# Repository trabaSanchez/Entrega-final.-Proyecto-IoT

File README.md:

# Entrega-final.-Proyecto-IoT
Este repositorio contiene el compendio final, desarrollado por los estudiantes de ingenieria, Cristian Montaño, Jhonatan Rodríguez e Iván Sánchez. Para la materia de diseño de dispositivos IoT.

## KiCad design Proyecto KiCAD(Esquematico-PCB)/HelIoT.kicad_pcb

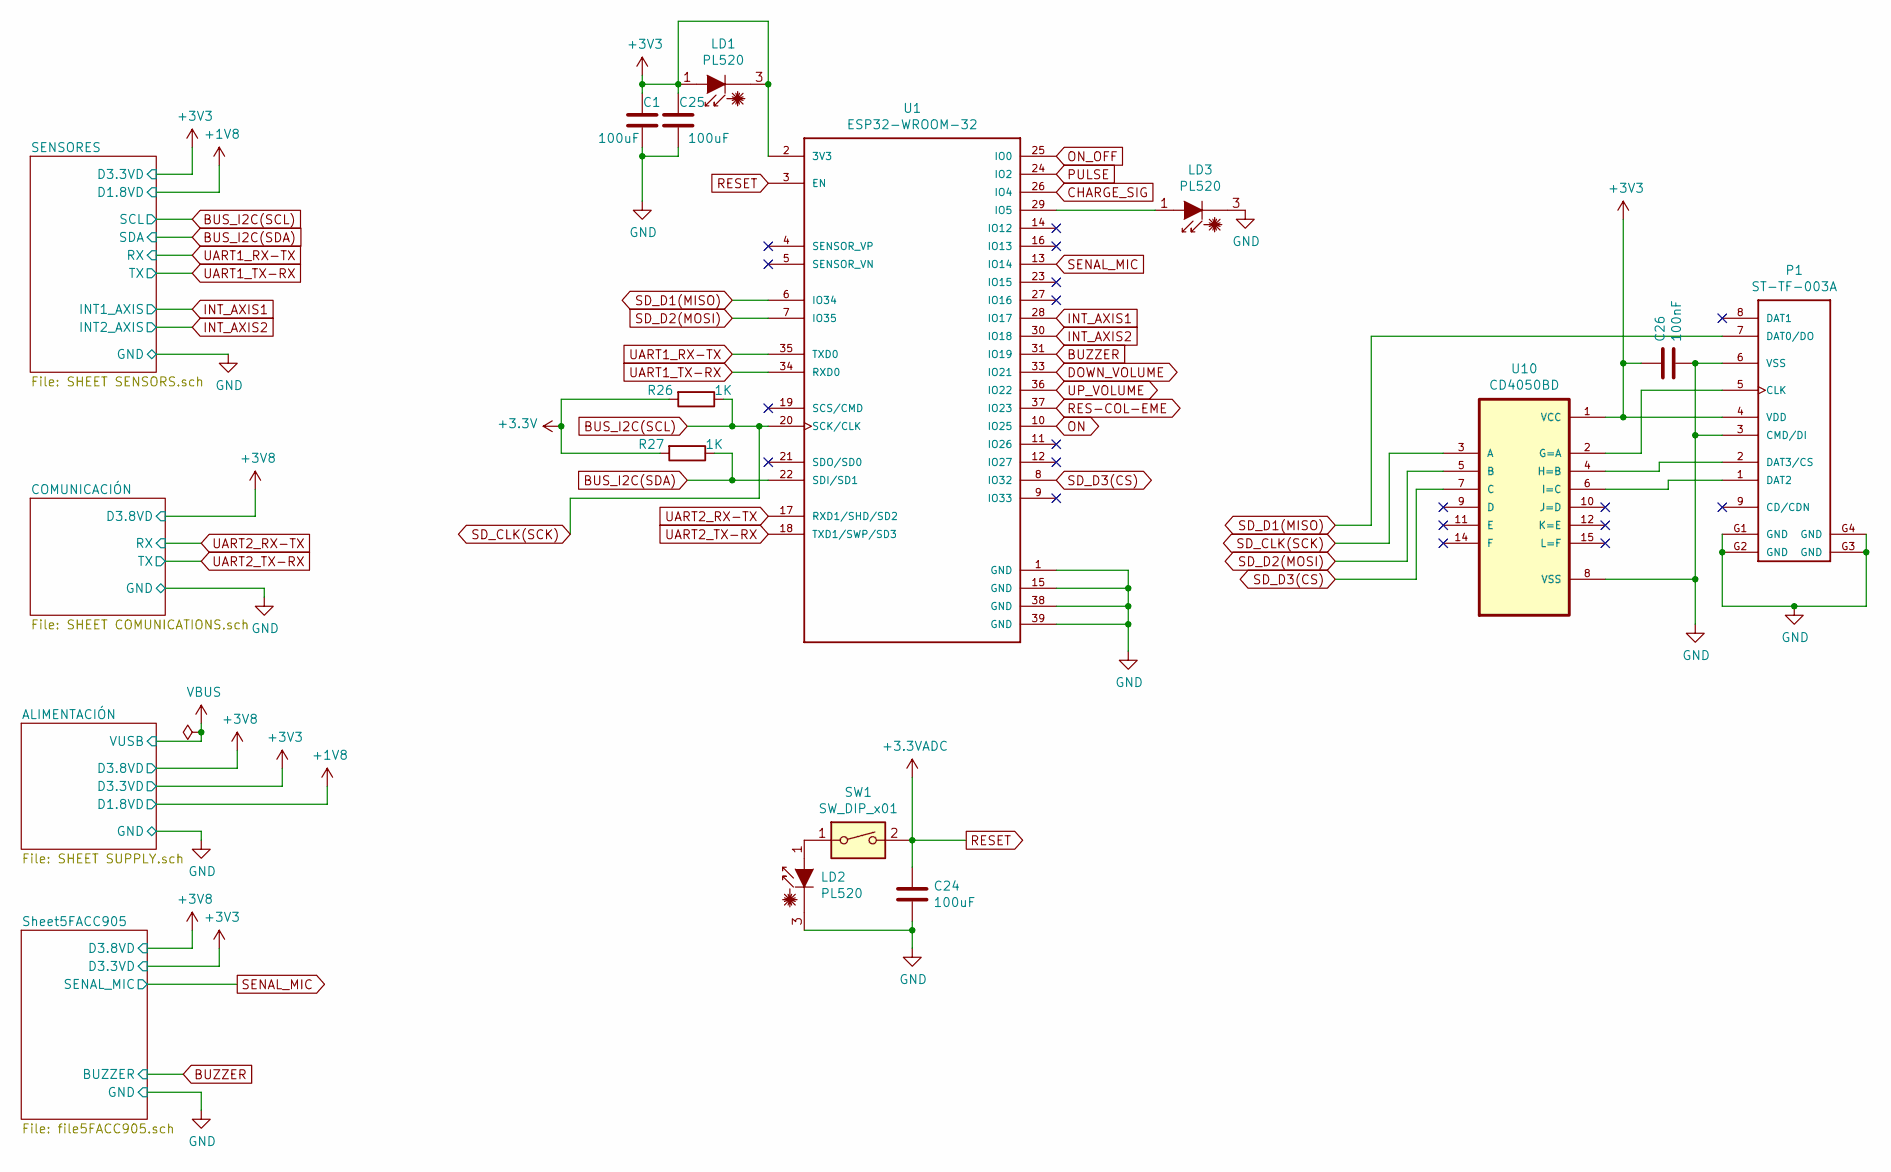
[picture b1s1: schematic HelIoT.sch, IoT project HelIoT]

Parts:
C1, C24, C25: 100uF; C_0603_1608Metric_Pad1.08x0.95mm_HandSolder
C26: 100nF; C_0603_1608Metric_Pad1.08x0.95mm_HandSolder
LD1, LD2, LD3: PL520; LaserDiode_TO38ICut-3
P1: ST-TF-003A; SUNTECH_ST-TF-003A
R26, R27: 1K; R_0402_1005Metric_Pad0.72x0.64mm_HandSolder
SW1: SW_DIP_x01; SW_SPST_REED_CT05-XXXX-G1
U1: ESP32-WROOM-32; MODULE_ESP32-WROOM-32
U10: CD4050BD; SOIC127P600X175-16N

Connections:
BUS_I2C(SCL): R26.1, U1.20 (SCK/CLK), U10.3 (A); also elsewhere on the board
BUS_I2C(SDA): R27.1, U1.22 (SDI/SD1); also elsewhere on the board
BUZZER: U1.31 (IO19); also elsewhere on the board
CHARGE_SIG: U1.26 (IO4); also elsewhere on the board
GND: C1.2, C24.2, C25.2, C26.2, LD2.3 (C), LD3.3 (C), P1.3 (CMD/DI), P1.6 (VSS), P1.G1 (GND), P1.G2 (GND), P1.G3 (GND), P1.G4 (GND), U1.1 (GND), U1.15 (GND), U1.38 (GND), U1.39 (GND), U10.8 (VSS); also elsewhere on the board
INT_AXIS1: U1.28 (IO17); also elsewhere on the board
INT_AXIS2: U1.30 (IO18); also elsewhere on the board
unnamed: LD2.1 (A), SW1.1
unnamed: LD3.1 (A), U1.29 (IO5)
unnamed: P1.1 (DAT2), U10.6 (I=C)
unnamed: P1.2 (DAT3/CS), U10.4 (H=B)
unnamed: P1.5 (CLK), U10.2 (G=A)
ON_OFF: U1.25 (IO0); also elsewhere on the board
PULSE: U1.24 (IO2); also elsewhere on the board
RESET: C24.1, SW1.2, U1.3 (EN); also elsewhere on the board
RXSIM: U1.18 (TXD1/SWP/SD3); also elsewhere on the board
SD_D1(MISO): P1.7 (DAT0/DO), U1.6 (IO34)
SD_D2(MOSI): U1.7 (IO35), U10.5 (B)
SD_D3(CS): U1.8 (IO32), U10.7 (C)
SENAL_MIC: U1.13 (IO14); also elsewhere on the board
TXSIM: U1.17 (RXD1/SHD/SD2); also elsewhere on the board
UART1_RX-TX: U1.35 (TXD0); also elsewhere on the board
UART1_TX-RX: U1.34 (RXD0); also elsewhere on the board
V2: C1.1, C25.1, C26.1, LD1.1 (A), LD1.3 (C), P1.4 (VDD), R26.2, R27.2, U1.2 (3V3), U10.1 (VCC); also elsewhere on the board

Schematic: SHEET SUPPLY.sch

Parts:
C2: 22uF; C_0504_1310Metric_Pad0.83x1.28mm_HandSolder
C3, C11: 1uF; C_0402_1005Metric_Pad0.74x0.62mm_HandSolder
C4: 10uF; C_0402_1005Metric_Pad0.74x0.62mm_HandSolder
C5: 22uF; C_0402_1005Metric_Pad0.74x0.62mm_HandSolder
C8, C9: 0.47uF; C_0402_1005Metric_Pad0.74x0.62mm_HandSolder
C10: 100uF; C_0603_1608Metric_Pad1.08x0.95mm_HandSolder
C12, C13: 0.1uF; C_0402_1005Metric_Pad0.74x0.62mm_HandSolder
C14: 4.7uF; C_0603_1608Metric_Pad1.08x0.95mm_HandSolder
D1: BZX84C3V3LTIG; D_SOT-23_ANK
J1: USB4085-GF-A_REVA; GCT_USB4085-GF-A_REVA
J2: BAT; BatteryHolder_MPD_BA9VPC_1xPP3
L1: 1uH; L_0603_1608Metric_Pad1.05x0.95mm_HandSolder
Q3: FFB3904; SOT-363_SC-70-6
Q4: FDN340P; SOT-23
R2, R4, R6, R7, R18, R20, R22, R23, R24, R32, R34: 100K; R_0603_1608Metric_Pad0.98x0.95mm_HandSolder
R3, R8, R17, R19, R21: 1K5; R_0402_1005Metric_Pad0.72x0.64mm_HandSolder
R5: 560K; R_0612_1632Metric_Pad1.18x3.40mm_HandSolder
R9: 680K; R_0612_1632Metric_Pad1.18x3.40mm_HandSolder
R10: 270K; R_0603_1608Metric_Pad0.98x0.95mm_HandSolder
R33: 10K; R_0603_1608Metric_Pad0.98x0.95mm_HandSolder
R35: 68K; R_0603_1608Metric_Pad0.98x0.95mm_HandSolder
SW6: SW_DIP_x01; SW_SPST_REED_CT05-XXXX-G1
TP1, TP2, TP3, TP4, TP5, TP6, TP7: TP; PinHeader_1x01_P1.00mm_Vertical
U2: BQ24075RGTR; QFN50P300X300X100-17N
U3: MP28164GD-P; MP28164GDP
U4: AP7340-25FS4-7; VREG_AP7340-25FS4-7; PARTREV 5 - 2
U5: MCP1793; SOT127P706X180-6N
U9: BAT54TW-7-F; SOT65P220X110-6N; MPN BAT54TW-7-F

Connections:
CHARGE_SIG: U2.4 (~CE); also elsewhere on the board
GND: C2.2, C3.1, C4.2, C5.2, C8.2, C9.2, C10.2, C11.2, C12.2, C13.2, C14.1, D1.2 (A), J1.A1 (GND), J1.A6 (DP1), J1.A7 (DN1), J1.A12 (GND), J1.B1 (GND), J1.B5 (CC2), J1.B6 (DP2), J1.B7 (DN2), J1.B12 (GND), J1.P1 (SHELL), J1.P2 (SHELL), J1.P3 (SHELL), J1.P4 (SHELL), J2.2, R2.2, R4.2, R6.2, R7.2, R9.2, R17.2, R18.2, R19.2, R20.2, U2.6 (EN1), U2.8 (VSS), U3.5, U3.9, U4.2 (GND), U5.3, U5.6; also elsewhere on the board
unnamed: C2.1, R3.2, U3.1, U3.11
unnamed: C3.2, U3.4
unnamed: C8.1, R8.2, U4.3 (EN), U4.4 (VIN)
unnamed: C10.1, J2.1, R10.1, TP7.1, U2.2 (BAT_2), U2.3 (BAT_3)
unnamed: C12.1, R21.2, U5.1, U5.2
unnamed: C14.2, Q4.2 (S), R34.2, U2.5 (EN2), U2.10 (OUT_10), U2.11 (OUT_11)
unnamed: D1.1 (K), R9.1, R10.2
unnamed: J1.A5 (CC1), R4.1
unnamed: L1.1, U3.10
unnamed: L1.2, U3.8
unnamed: Q3.1 (E1), R32.1, SW6.2
unnamed: Q3.2 (B1), R33.1
unnamed: Q3.6 (C1), U9.4 (C3)
unnamed: Q4.1 (G), R34.1, U9.2 (A2), U9.3 (A3)
unnamed: R5.2, R6.1, U3.6
unnamed: R17.1, U2.12 (ILIM)
unnamed: R18.1, U2.1 (TS)
unnamed: R19.1, U2.16 (ISET)
unnamed: R22.2, U2.9 (~CHG)
unnamed: R23.2, U2.15 (SYSOFF)
unnamed: R24.2, U2.7 (~PGOOD)
unnamed: R35.2, U9.6 (C1)
ON_OFF: R32.2, R33.2; also elsewhere on the board
PULSE: R35.1, SW6.1, TP6.1, U9.5 (C2); also elsewhere on the board
V1: C5.1, R5.1, R7.1, R8.1, R20.1, R21.1, TP1.1, U3.7; also elsewhere on the board
V2: C13.1, R22.1, R24.1, TP4.1, U5.4, U9.1 (A1); also elsewhere on the board
V3: C9.1, TP3.1, U4.1 (VOUT); also elsewhere on the board
VOUT: Q4.3 (D), R2.1, R3.1, TP5.1
VUSB: C4.1, C11.1, J1.A4 (VBUS), J1.A9 (VBUS), J1.B4 (VBUS), J1.B9 (VBUS), R23.1, TP2.1, U2.13 (IN)

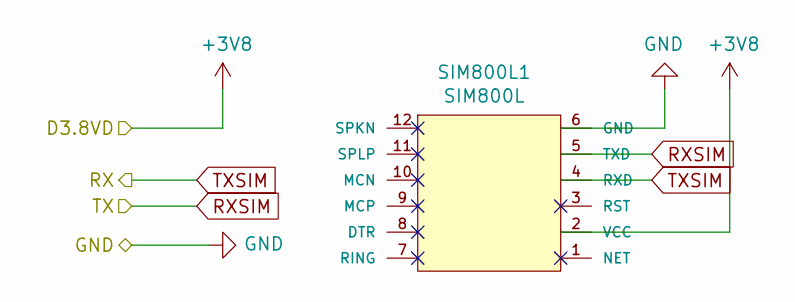
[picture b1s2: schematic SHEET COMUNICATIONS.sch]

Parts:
SIM800L1: SIM800L; SIM800L1

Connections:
GND: SIM800L1.6 (GND); also elsewhere on the board
RXSIM: SIM800L1.5 (TXD); also elsewhere on the board
TXSIM: SIM800L1.4 (RXD); also elsewhere on the board
V1: SIM800L1.2 (VCC); also elsewhere on the board

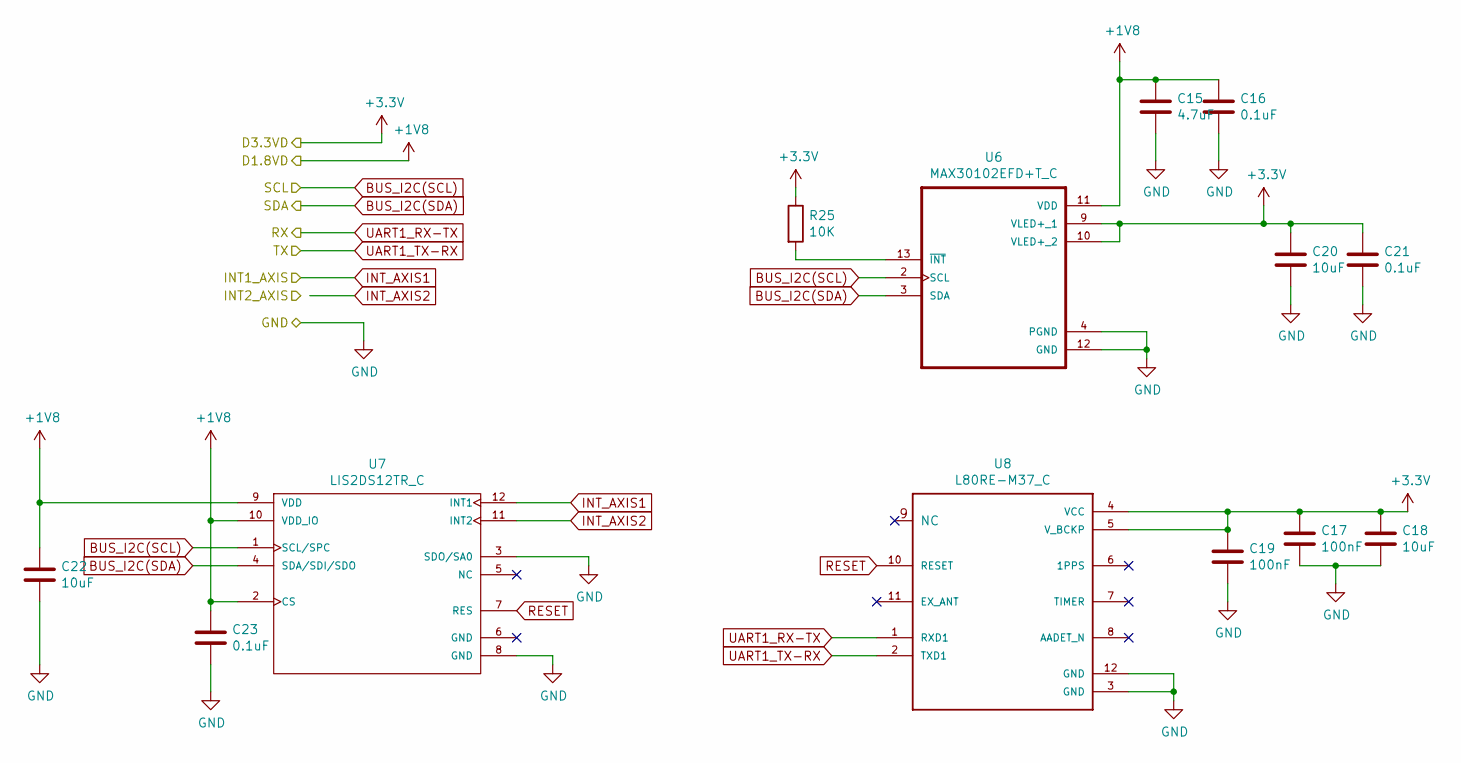
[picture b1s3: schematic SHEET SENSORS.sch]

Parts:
C15: 4.7uF; C_0603_1608Metric_Pad1.08x0.95mm_HandSolder
C16, C21, C23: 0.1uF; C_0402_1005Metric_Pad0.74x0.62mm_HandSolder
C17, C19: 100nF; C_0603_1608Metric_Pad1.08x0.95mm_HandSolder
C18, C20: 10uF; C_0603_1608Metric_Pad1.08x0.95mm_HandSolder
C22: 10uF; C_0504_1310Metric_Pad0.83x1.28mm_HandSolder
R25: 10K; R_0603_1608Metric_Pad0.98x0.95mm_HandSolder
U6: MAX30102EFD+T_C; XDCR_MAX30101EFD+
U7: LIS2DS12TR_C; LGA12R50P4X4_200X200X86
U8: L80RE-M37_C; XCVR_L80RE-M37

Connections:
BUS_I2C(SCL): U6.2 (SCL), U7.1 (SCL/SPC); also elsewhere on the board
BUS_I2C(SDA): U6.3 (SDA), U7.4 (SDA/SDI/SDO); also elsewhere on the board
GND: C15.2, C16.2, C17.2, C18.2, C19.2, C20.2, C21.2, C22.2, C23.2, U6.4 (PGND), U6.12 (GND), U7.3 (SDO/SA0), U7.8 (GND), U8.3 (GND), U8.12 (GND); also elsewhere on the board
INT_AXIS1: U7.12 (INT1); also elsewhere on the board
INT_AXIS2: U7.11 (INT2); also elsewhere on the board
unnamed: R25.2, U6.13 (~INT~)
RESET: U7.7 (RES), U8.10 (RESET); also elsewhere on the board
UART1_RX-TX: U8.1 (RXD1); also elsewhere on the board
UART1_TX-RX: U8.2 (TXD1); also elsewhere on the board
V2: C17.1, C18.1, C19.1, C20.1, C21.1, R25.1, U6.9 (VLED+_1), U6.10 (VLED+_2), U8.4 (VCC), U8.5 (V_BCKP); also elsewhere on the board
V3: C15.1, C16.1, C22.1, C23.1, U6.11 (VDD), U7.2 (CS), U7.9 (VDD), U7.10 (VDD_IO); also elsewhere on the board

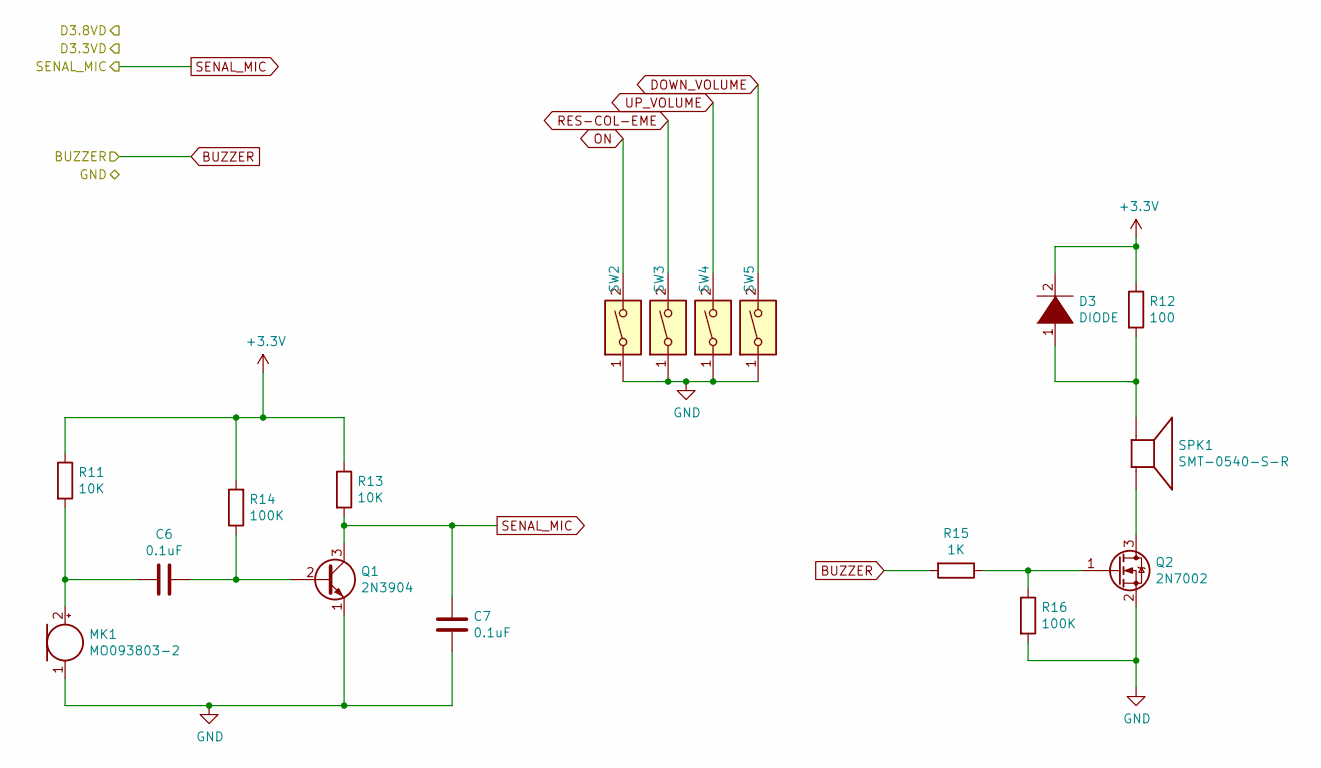
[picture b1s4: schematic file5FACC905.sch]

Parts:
C6, C7: 0.1uF; C_0402_1005Metric_Pad0.74x0.62mm_HandSolder
D3: DIODE; D_0201_0603Metric_Pad0.64x0.40mm_HandSolder
MK1: MO093803-2; PinSocket_1x02_P2.54mm_Horizontal
Q1: 2N3904; TO-92_Inline
Q2: 2N7002; SOT-23
R11, R13: 10K; R_0603_1608Metric_Pad0.98x0.95mm_HandSolder
R12: 100; R_0603_1608Metric_Pad0.98x0.95mm_HandSolder
R14, R16: 100K; R_0603_1608Metric_Pad0.98x0.95mm_HandSolder
R15: 1K; R_0402_1005Metric_Pad0.72x0.64mm_HandSolder
SPK1: SMT-0540-S-R; PinHeader_2x01_P2.00mm_Horizontal
SW2, SW3, SW4, SW5: SW_DIP_x01; SW_SPST_REED_CT05-XXXX-G1

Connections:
BUZZER: R15.2; also elsewhere on the board
GND: C7.2, MK1.1 (-), Q1.1 (E), Q2.2 (S), R16.2, SW2.1, SW3.1, SW4.1, SW5.1; also elsewhere on the board
unnamed: C6.1, Q1.2 (B), R14.1
unnamed: C6.2, MK1.2 (+), R11.2
unnamed: D3.1 (K), R12.2, SPK1.-
unnamed: Q2.1 (G), R15.1, R16.1
unnamed: Q2.3 (D), SPK1.+
SENAL_MIC: C7.1, Q1.3 (C), R13.2; also elsewhere on the board
V2: D3.2 (A), R11.1, R12.1, R13.1, R14.2; also elsewhere on the board

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
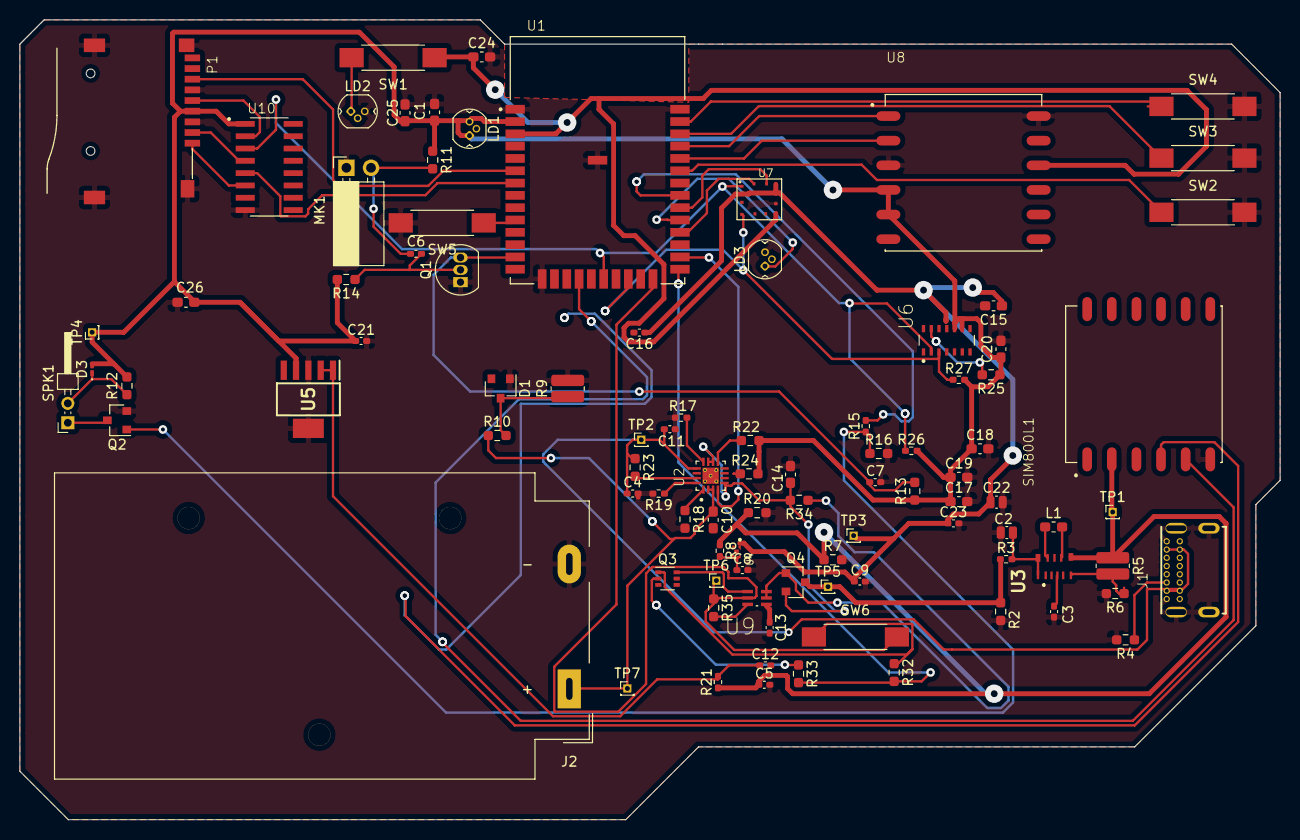
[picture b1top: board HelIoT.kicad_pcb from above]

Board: 2 copper layers, 130.0 x 82.5 mm, 95 parts (0 on the bottom side), 60 nets.

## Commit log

2020-12-07 Agregamos documentación así como resultados del proyecto HELIoT
